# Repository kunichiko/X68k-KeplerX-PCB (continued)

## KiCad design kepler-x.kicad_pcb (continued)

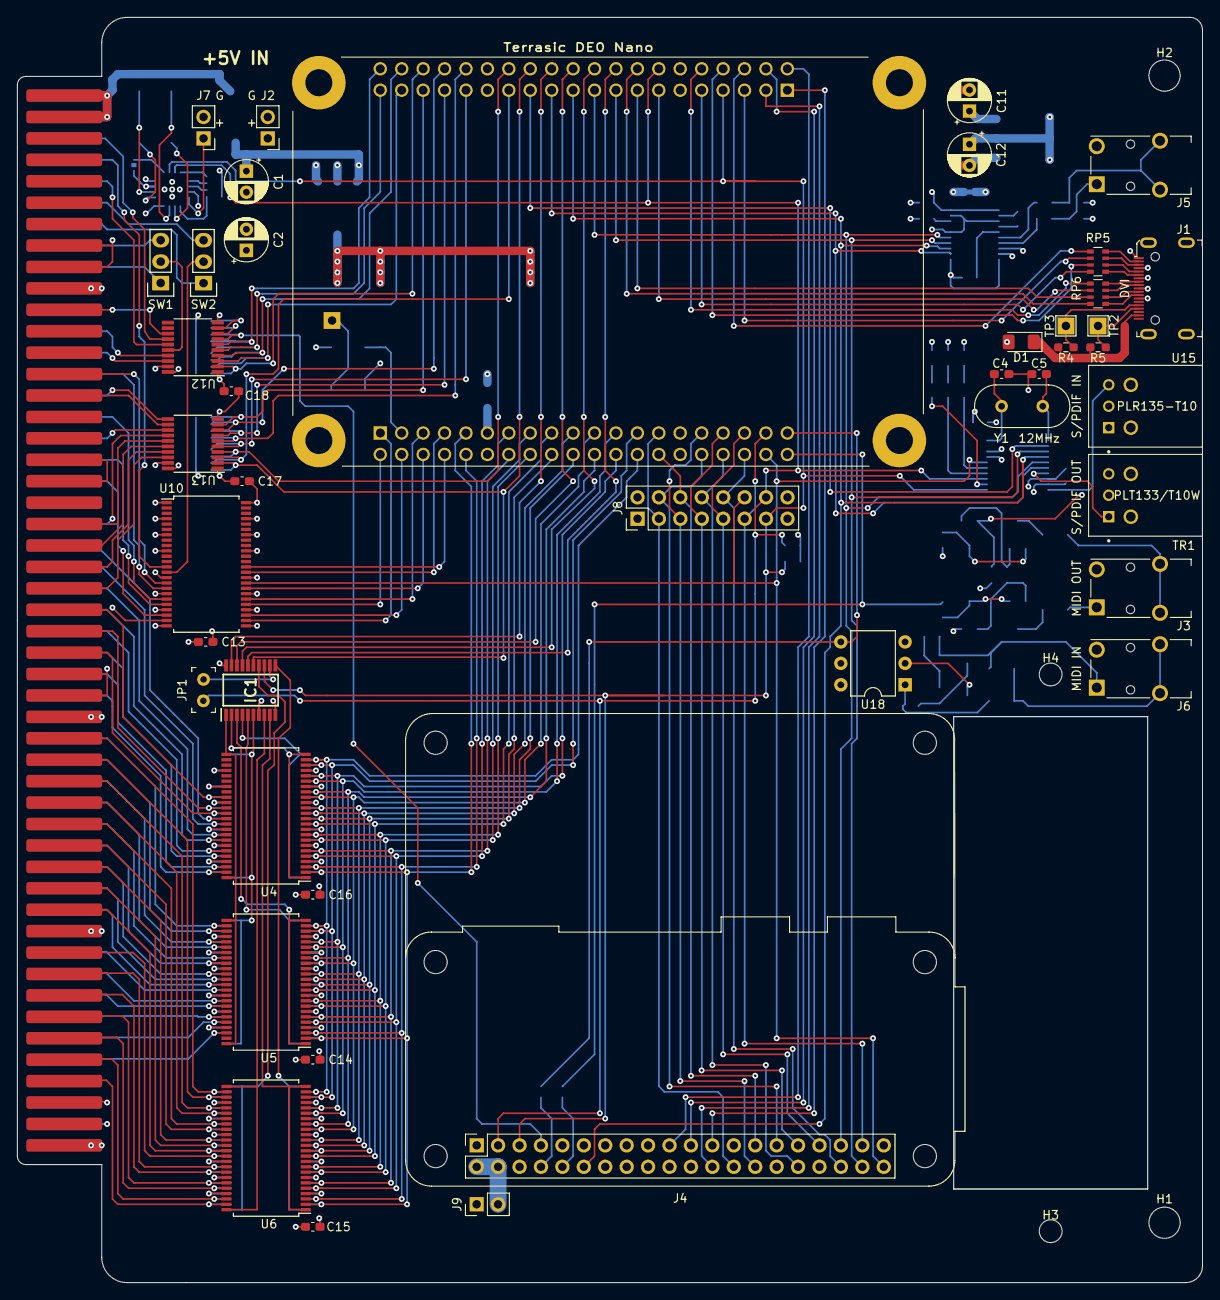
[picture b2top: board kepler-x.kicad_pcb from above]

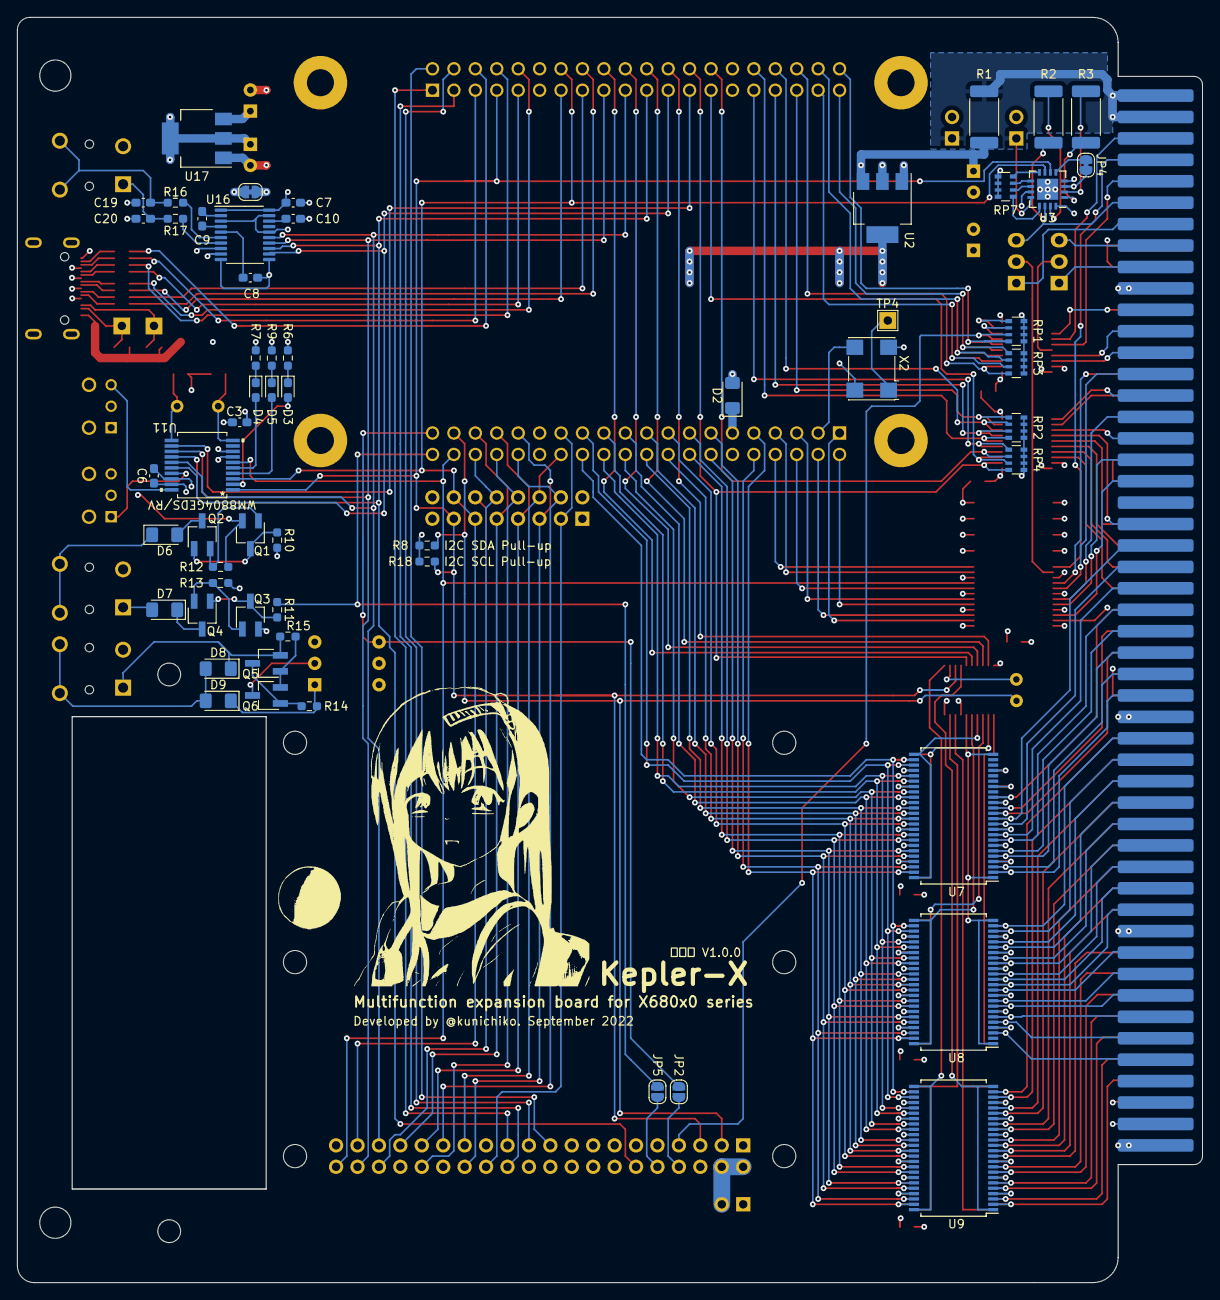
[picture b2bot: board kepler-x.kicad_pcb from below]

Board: 4 copper layers, 140.5 x 150.0 mm, 105 parts (57 on the bottom side), 218 nets.

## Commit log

2022-09-06 Today's version
2022-09-07 Add fooprints
2022-09-08 Change submodule url
2022-09-08 Update submodules
2022-09-18 DRC free version
2022-09-18 Alpha version
2022-09-18 current version (DE0 Nano is upside down :-( )
2022-09-18 Fix upside down foot print.
2022-09-19 Fix for v1.0.0
2022-09-19 Ver 1.0.0 RC1
2022-09-21 V1.0.0 RC2
2022-09-21 v1.0.0 (ordered 2022/9/22)
2022-09-23 Fixed the board can accept TC7MPB9307FT or TC7MPB9307FK.
2022-09-23 Add MIDI I/F silk print.
2022-12-31 Commit current status
2023-01-05 - フォルダ構造を変更 - コントローラー基板を追加 - 弍號機の敗戦を開始
2023-01-06 revert submodules
2023-01-06 Change library path
2023-01-07 v2.0.0 RC1
2023-01-07 v2.0.0 RC2
2023-01-08 v2.0.0 production data
2023-01-09 3.5mmジャックの Tipと Ringが逆になっていた問題などを修正
2023-01-10 再再度出し直し(v2.0.2)
2023-01-11 Fixed interchanged silkscreens of FB3 and C30.
2023-08-16 現状をコミット
2023-08-30 V3.0.0
2023-09-01 V3.0.0 (Fixed)
2023-10-13 v1.0.1 - Changed one of the two sets of open jumper pairs to a bridged jumper
2023-12-03 Llast commit ussing TSSOP20 package for CH32V003
2023-12-04 V3.0.1
2025-01-11 MSXカートリッジリーダーの回路をかきはじめた
